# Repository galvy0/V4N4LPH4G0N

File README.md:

# V4N4LPH4G0N

Alpha stagger version of the V4N4G0N.  

Heavily referenced V4N4G0RTH0N: https://github.com/jpuerto96/V4N4G0RTH0N

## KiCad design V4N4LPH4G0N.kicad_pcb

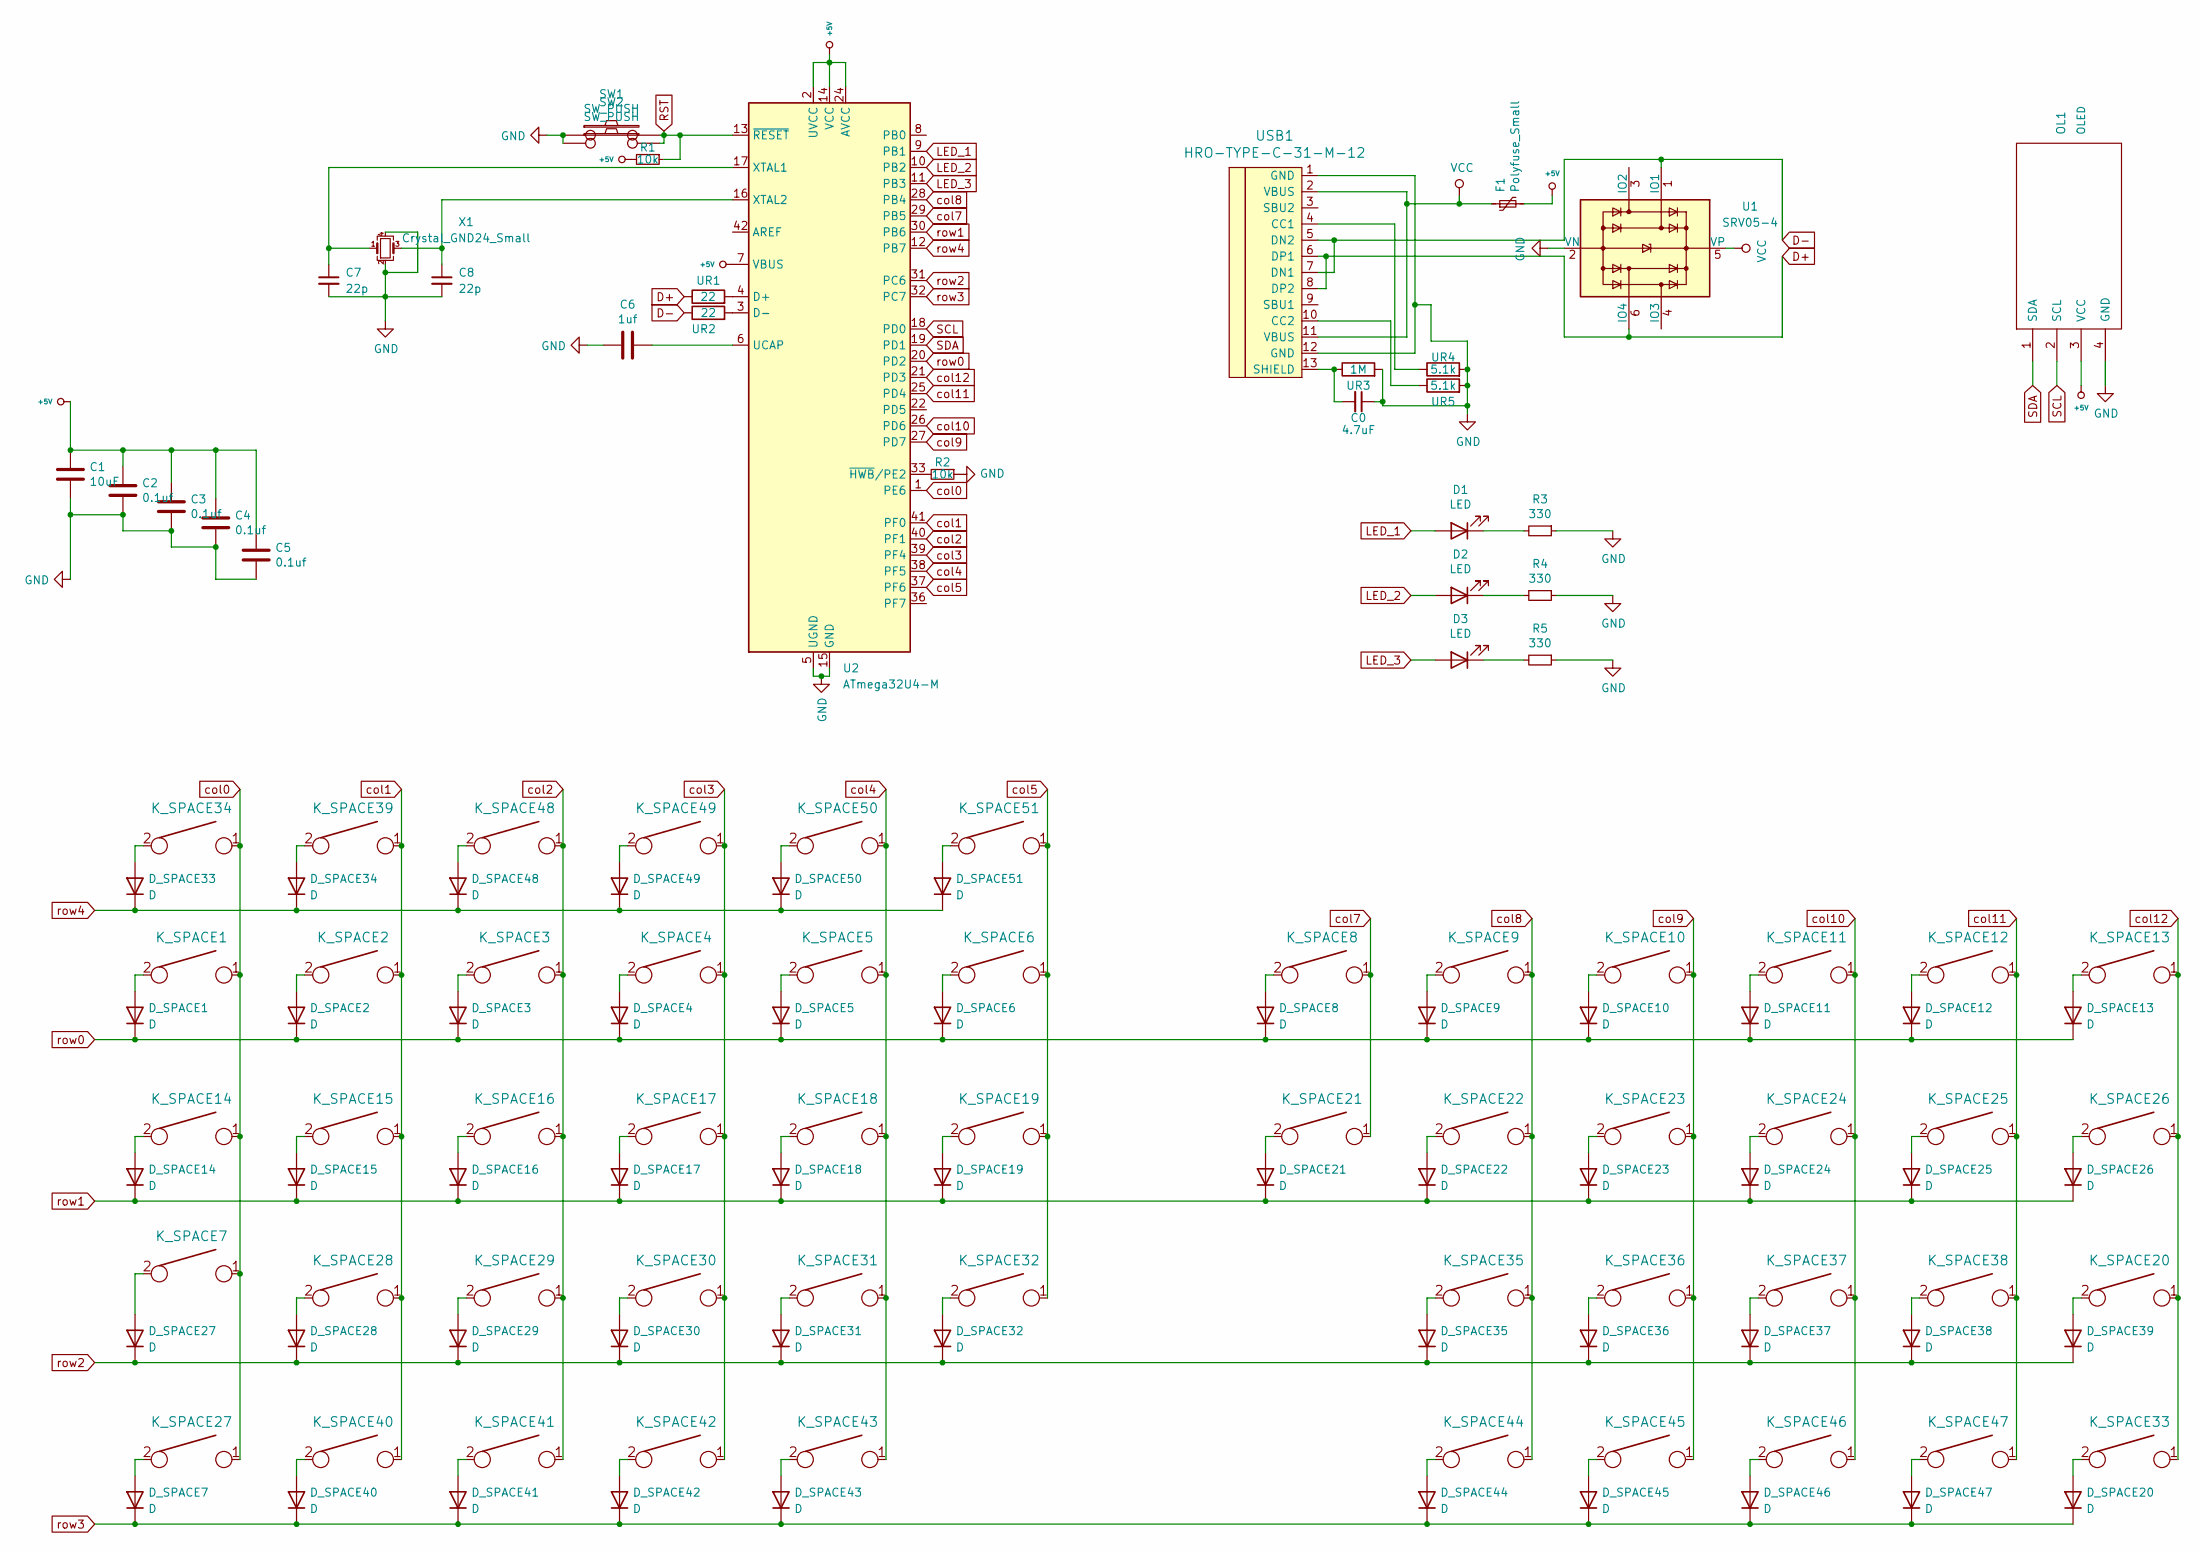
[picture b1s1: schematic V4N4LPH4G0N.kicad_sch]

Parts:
C0: 4.7uF; C_0805_2012Metric_Pad1.18x1.45mm_HandSolder
C1: 10uF; C_0805_2012Metric_Pad1.18x1.45mm_HandSolder
C2, C3, C4, C5: 0.1uf; C_0805_2012Metric_Pad1.18x1.45mm_HandSolder
C6: 1uf; C_0805_2012Metric_Pad1.18x1.45mm_HandSolder
C7, C8: 22p; C_0805_2012Metric_Pad1.18x1.45mm_HandSolder
D1, D2, D3: LED; LED_D3.0mm
D_SPACE1, D_SPACE2, D_SPACE3, D_SPACE4, D_SPACE5, D_SPACE6, D_SPACE7, D_SPACE8, D_SPACE9, D_SPACE10, D_SPACE11, D_SPACE12, D_SPACE13, D_SPACE14, D_SPACE15, D_SPACE16, D_SPACE17, D_SPACE18, D_SPACE19, D_SPACE20, D_SPACE21, D_SPACE22, D_SPACE23, D_SPACE24, D_SPACE25, D_SPACE26, D_SPACE27, D_SPACE28, D_SPACE29, D_SPACE30, D_SPACE31, D_SPACE32, D_SPACE33, D_SPACE34, D_SPACE35, D_SPACE36, D_SPACE37, D_SPACE38, D_SPACE39, D_SPACE40, D_SPACE41, D_SPACE42, D_SPACE43, D_SPACE44, D_SPACE45, D_SPACE46, D_SPACE47, D_SPACE48, D_SPACE49, D_SPACE50, D_SPACE51: D; D_SOD-123
F1: Polyfuse_Small; Fuse_1206_3216Metric_Pad1.42x1.75mm_HandSolder
K_SPACE1, K_SPACE2, K_SPACE3, K_SPACE4, K_SPACE5, K_SPACE6, K_SPACE8, K_SPACE9, K_SPACE10, K_SPACE11, K_SPACE12, K_SPACE13, K_SPACE14, K_SPACE15, K_SPACE16, K_SPACE17, K_SPACE18, K_SPACE19, K_SPACE21, K_SPACE22, K_SPACE23, K_SPACE24, K_SPACE25, K_SPACE26, K_SPACE28, K_SPACE29, K_SPACE30, K_SPACE31, K_SPACE34, K_SPACE35, K_SPACE36, K_SPACE37, K_SPACE38, K_SPACE39, K_SPACE42, K_SPACE45, K_SPACE48, K_SPACE49, K_SPACE50, K_SPACE51: KEYSW; MXOnly-1U-NoLED
K_SPACE7, K_SPACE20, K_SPACE43: KEYSW; MXOnly-1.5U-NoLED
K_SPACE27, K_SPACE33, K_SPACE40, K_SPACE41, K_SPACE46, K_SPACE47: KEYSW; MXOnly-1.25U-NoLED
K_SPACE32, K_SPACE44: KEYSW; MXOnly-1.75U-NoLED
OL1: OLED; OLED_v2
R1, R2: 10k; R_0805_2012Metric_Pad1.20x1.40mm_HandSolder
R3, R4, R5: 330; R_0805_2012Metric
SW1, SW2: SW_PUSH; SW_SPST_SKQG_WithoutStem
U1: SRV05-4; SOT-23-6_Handsoldering
U2: ATmega32U4-M; QFN-44-1EP_7x7mm_P0.5mm_EP5.2x5.2mm_ThermalVias
UR1, UR2: 22; R_0805_2012Metric_Pad1.20x1.40mm_HandSolder
UR3: 1M; R_0805_2012Metric_Pad1.20x1.40mm_HandSolder
UR4, UR5: 5.1k; R_0805_2012Metric_Pad1.20x1.40mm_HandSolder
USB1: HRO-TYPE-C-31-M-12; HRO-TYPE-C-31-M-12-HandSoldering
X1: Crystal_GND24_Small; Crystal_SMD_3225-4Pin_3.2x2.5mm_HandSoldering

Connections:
+5V: C1.1, C2.1, C3.1, C4.1, C5.1, F1.2, OL1.3 (VCC), R1.2, U2.2 (UVCC), U2.7 (VBUS), U2.14 (VCC), U2.24 (AVCC), U2.34 (VCC), U2.44 (AVCC)
D+: U1.6 (IO4), UR2.1, USB1.6 (DP1), USB1.8 (DP2)
D-: U1.1 (IO1), UR1.1, USB1.5 (DN2), USB1.7 (DN1)
GND: C0.1, C1.2, C2.2, C3.2, C4.2, C5.2, C6.2, C7.2, C8.2, OL1.4 (GND), R2.1, R3.1, R4.1, R5.1, SW1.1, SW2.1, U1.2 (VN), U2.5 (UGND), U2.15 (GND), U2.23 (GND), U2.35 (GND), U2.43 (GND), U2.45 (GND), UR3.2, UR4.2, UR5.2, USB1.1 (GND), USB1.12 (GND), X1.2, X1.4
LED_1: D1.2 (A), U2.9 (PB1)
LED_2: D2.2 (A), U2.10 (PB2)
LED_3: D3.2 (A), U2.11 (PB3)
unnamed: C0.2, UR3.1, USB1.13 (SHIELD)
unnamed: C6.1, U2.6 (UCAP)
unnamed: C7.1, U2.17 (XTAL1), X1.1
unnamed: C8.1, U2.16 (XTAL2), X1.3
unnamed: D1.1 (K), R3.2
unnamed: D2.1 (K), R4.2
unnamed: D3.1 (K), R5.2
unnamed: D_SPACE1.2 (A), K_SPACE1.2
unnamed: D_SPACE2.2 (A), K_SPACE2.2
unnamed: D_SPACE3.2 (A), K_SPACE3.2
unnamed: D_SPACE4.2 (A), K_SPACE4.2
unnamed: D_SPACE5.2 (A), K_SPACE5.2
unnamed: D_SPACE6.2 (A), K_SPACE6.2
unnamed: D_SPACE7.2 (A), K_SPACE27.2
unnamed: D_SPACE8.2 (A), K_SPACE8.2
unnamed: D_SPACE9.2 (A), K_SPACE9.2
unnamed: D_SPACE10.2 (A), K_SPACE10.2
unnamed: D_SPACE11.2 (A), K_SPACE11.2
unnamed: D_SPACE12.2 (A), K_SPACE12.2
unnamed: D_SPACE13.2 (A), K_SPACE13.2
unnamed: D_SPACE14.2 (A), K_SPACE14.2
unnamed: D_SPACE15.2 (A), K_SPACE15.2
unnamed: D_SPACE16.2 (A), K_SPACE16.2
unnamed: D_SPACE17.2 (A), K_SPACE17.2
unnamed: D_SPACE18.2 (A), K_SPACE18.2
unnamed: D_SPACE19.2 (A), K_SPACE19.2
unnamed: D_SPACE20.2 (A), K_SPACE33.2
unnamed: D_SPACE21.2 (A), K_SPACE21.2
unnamed: D_SPACE22.2 (A), K_SPACE22.2
unnamed: D_SPACE23.2 (A), K_SPACE23.2
unnamed: D_SPACE24.2 (A), K_SPACE24.2
unnamed: D_SPACE25.2 (A), K_SPACE25.2
unnamed: D_SPACE26.2 (A), K_SPACE26.2
unnamed: D_SPACE27.2 (A), K_SPACE7.2
unnamed: D_SPACE28.2 (A), K_SPACE28.2
unnamed: D_SPACE29.2 (A), K_SPACE29.2
unnamed: D_SPACE30.2 (A), K_SPACE30.2
unnamed: D_SPACE31.2 (A), K_SPACE31.2
unnamed: D_SPACE32.2 (A), K_SPACE32.2
unnamed: D_SPACE33.2 (A), K_SPACE34.2
unnamed: D_SPACE34.2 (A), K_SPACE39.2
unnamed: D_SPACE35.2 (A), K_SPACE35.2
unnamed: D_SPACE36.2 (A), K_SPACE36.2
unnamed: D_SPACE37.2 (A), K_SPACE37.2
unnamed: D_SPACE38.2 (A), K_SPACE38.2
unnamed: D_SPACE39.2 (A), K_SPACE20.2
unnamed: D_SPACE40.2 (A), K_SPACE40.2
unnamed: D_SPACE41.2 (A), K_SPACE41.2
unnamed: D_SPACE42.2 (A), K_SPACE42.2
unnamed: D_SPACE43.2 (A), K_SPACE43.2
unnamed: D_SPACE44.2 (A), K_SPACE44.2
unnamed: D_SPACE45.2 (A), K_SPACE45.2
unnamed: D_SPACE46.2 (A), K_SPACE46.2
unnamed: D_SPACE47.2 (A), K_SPACE47.2
unnamed: D_SPACE48.2 (A), K_SPACE48.2
unnamed: D_SPACE49.2 (A), K_SPACE49.2
unnamed: D_SPACE50.2 (A), K_SPACE50.2
unnamed: D_SPACE51.2 (A), K_SPACE51.2
unnamed: R2.2, U2.33 (~HWB/PE2)
unnamed: U2.3 (D-), UR1.2
unnamed: U2.4 (D+), UR2.2
unnamed: UR4.1, USB1.4 (CC1)
unnamed: UR5.1, USB1.10 (CC2)
RST: R1.1, SW1.2, SW2.2, U2.13 (~RESET)
SCL: OL1.2 (SCL), U2.18 (PD0)
SDA: OL1.1 (SDA), U2.19 (PD1)
VCC: F1.1, U1.5 (VP), USB1.2 (VBUS), USB1.11 (VBUS)
col0: K_SPACE1.1, K_SPACE7.1, K_SPACE14.1, K_SPACE27.1, K_SPACE34.1, U2.1 (PE6)
col1: K_SPACE2.1, K_SPACE15.1, K_SPACE28.1, K_SPACE39.1, K_SPACE40.1, U2.41 (PF0)
col2: K_SPACE3.1, K_SPACE16.1, K_SPACE29.1, K_SPACE41.1, K_SPACE48.1, U2.40 (PF1)
col3: K_SPACE4.1, K_SPACE17.1, K_SPACE30.1, K_SPACE42.1, K_SPACE49.1, U2.39 (PF4)
col4: K_SPACE5.1, K_SPACE18.1, K_SPACE31.1, K_SPACE43.1, K_SPACE50.1, U2.38 (PF5)
col5: K_SPACE6.1, K_SPACE19.1, K_SPACE32.1, K_SPACE51.1, U2.37 (PF6)
col7: K_SPACE8.1, K_SPACE21.1, U2.29 (PB5)
col8: K_SPACE9.1, K_SPACE22.1, K_SPACE35.1, K_SPACE44.1, U2.28 (PB4)
col9: K_SPACE10.1, K_SPACE23.1, K_SPACE36.1, K_SPACE45.1, U2.27 (PD7)
col10: K_SPACE11.1, K_SPACE24.1, K_SPACE37.1, K_SPACE46.1, U2.26 (PD6)
col11: K_SPACE12.1, K_SPACE25.1, K_SPACE38.1, K_SPACE47.1, U2.25 (PD4)
col12: K_SPACE13.1, K_SPACE20.1, K_SPACE26.1, K_SPACE33.1, U2.21 (PD3)
row0: D_SPACE1.1 (K), D_SPACE2.1 (K), D_SPACE3.1 (K), D_SPACE4.1 (K), D_SPACE5.1 (K), D_SPACE6.1 (K), D_SPACE8.1 (K), D_SPACE9.1 (K), D_SPACE10.1 (K), D_SPACE11.1 (K), D_SPACE12.1 (K), D_SPACE13.1 (K), U2.20 (PD2)
row1: D_SPACE14.1 (K), D_SPACE15.1 (K), D_SPACE16.1 (K), D_SPACE17.1 (K), D_SPACE18.1 (K), D_SPACE19.1 (K), D_SPACE21.1 (K), D_SPACE22.1 (K), D_SPACE23.1 (K), D_SPACE24.1 (K), D_SPACE25.1 (K), D_SPACE26.1 (K), U2.30 (PB6)
row2: D_SPACE27.1 (K), D_SPACE28.1 (K), D_SPACE29.1 (K), D_SPACE30.1 (K), D_SPACE31.1 (K), D_SPACE32.1 (K), D_SPACE35.1 (K), D_SPACE36.1 (K), D_SPACE37.1 (K), D_SPACE38.1 (K), D_SPACE39.1 (K), U2.31 (PC6)
row3: D_SPACE7.1 (K), D_SPACE20.1 (K), D_SPACE40.1 (K), D_SPACE41.1 (K), D_SPACE42.1 (K), D_SPACE43.1 (K), D_SPACE44.1 (K), D_SPACE45.1 (K), D_SPACE46.1 (K), D_SPACE47.1 (K), U2.32 (PC7)
row4: D_SPACE33.1 (K), D_SPACE34.1 (K), D_SPACE48.1 (K), D_SPACE49.1 (K), D_SPACE50.1 (K), D_SPACE51.1 (K), U2.12 (PB7)

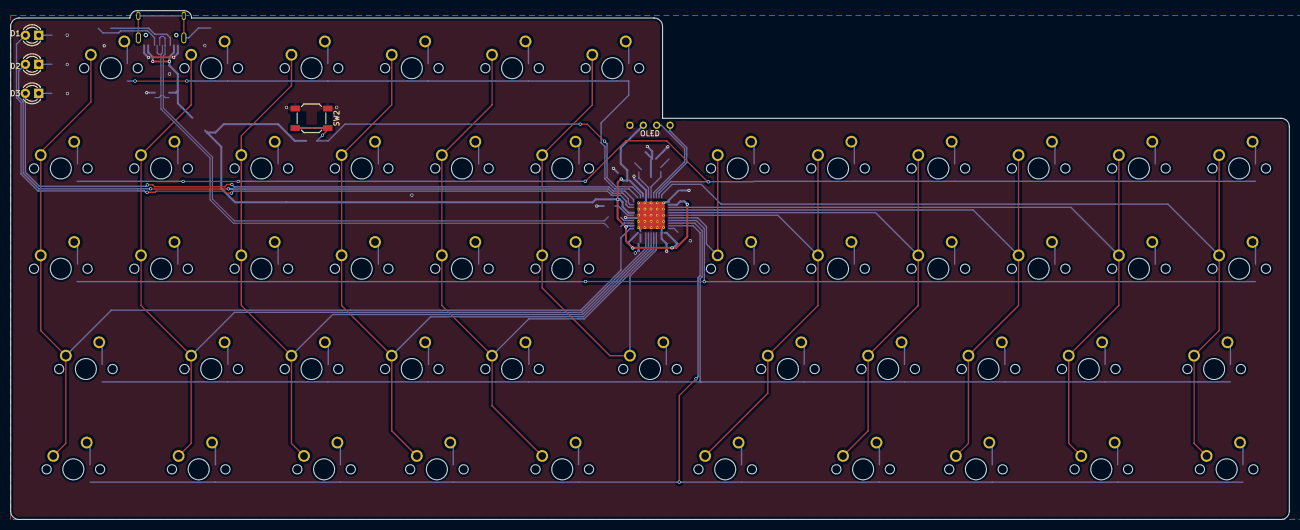
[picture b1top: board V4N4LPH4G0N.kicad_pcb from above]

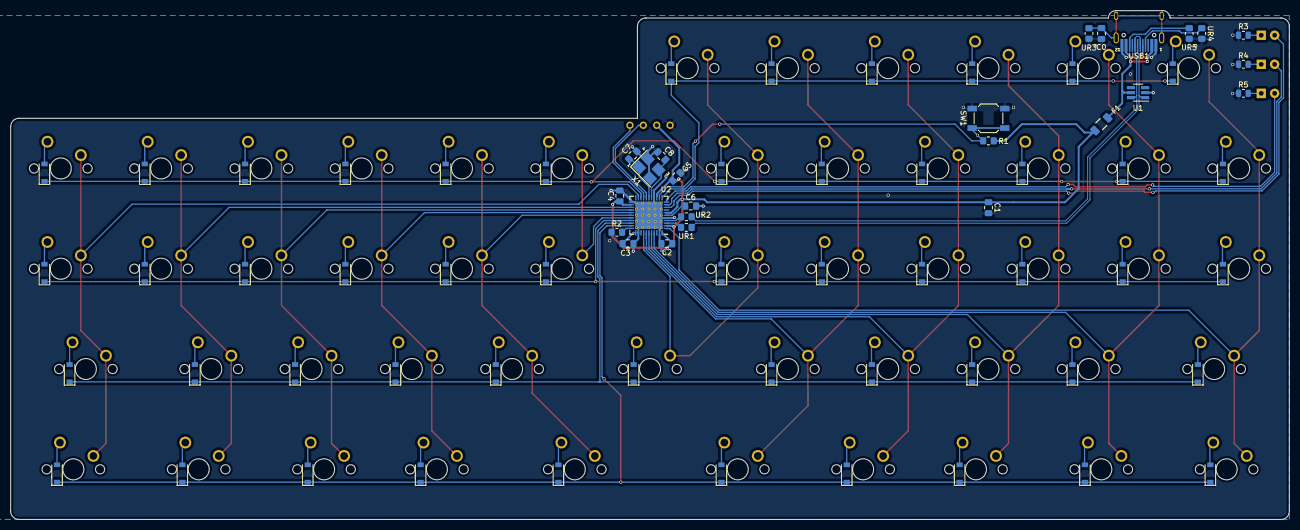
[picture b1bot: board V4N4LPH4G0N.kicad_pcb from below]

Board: 2 copper layers, 242.9 x 96.6 mm, 132 parts (76 on the bottom side), 91 nets.

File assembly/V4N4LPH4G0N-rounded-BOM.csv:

sep=;
"Id";"Designator";"Package";"Quantity";"Designation";"Supplier and ref";
1;"K_SPACE30,K_SPACE31,K_SPACE38,K_SPACE22,K_SPACE11,K_SPACE42,K_SPACE1,K_SPACE51,K_SPACE12,K_SPACE2,K_SPACE50,K_SPACE10,K_SPACE37,K_SPACE34,K_SPACE24,K_SPACE9,K_SPACE15,K_SPACE48,K_SPACE17,K_SPACE16,K_SPACE25,K_SPACE21,K_SPACE28,K_SPACE35,K_SPACE6,K_SPACE14,K_SPACE49,K_SPACE3,K_SPACE19,K_SPACE13,K_SPACE5,K_SPACE26,K_SPACE39,K_SPACE36,K_SPACE18,K_SPACE45,K_SPACE8,K_SPACE29,K_SPACE23,K_SPACE4";"MXOnly-1U-NoLED";40;"KEYSW";;;
2;"K_SPACE40,K_SPACE46,K_SPACE33,K_SPACE41,K_SPACE27,K_SPACE47";"MXOnly-1.25U-NoLED";6;"KEYSW";;;
3;"SW2,SW1";"SW_SPST_SKQG_WithoutStem";2;"SW_PUSH";;;
4;"D3,D2,D1";"LED_D3.0mm";3;"LED";;;
5;"K_SPACE43,K_SPACE7,K_SPACE20";"MXOnly-1.5U-NoLED";3;"KEYSW";;;
6;"K_SPACE44,K_SPACE32";"MXOnly-1.75U-NoLED";2;"KEYSW";;;
7;"OL1";"OLED_v2";1;"OLED";;;
8;"D_SPACE29,D_SPACE50,D_SPACE30,D_SPACE44,D_SPACE26,D_SPACE22,D_SPACE16,D_SPACE13,D_SPACE43,D_SPACE45,D_SPACE33,D_SPACE20,D_SPACE34,D_SPACE7,D_SPACE25,D_SPACE28,D_SPACE39,D_SPACE2,D_SPACE14,D_SPACE46,D_SPACE11,D_SPACE4,D_SPACE8,D_SPACE19,D_SPACE42,D_SPACE12,D_SPACE23,D_SPACE36,D_SPACE32,D_SPACE3,D_SPACE24,D_SPACE31,D_SPACE37,D_SPACE38,D_SPACE10,D_SPACE6,D_SPACE5,D_SPACE27,D_SPACE41,D_SPACE35,D_SPACE21,D_SPACE49,D_SPACE18,D_SPACE9,D_SPACE17,D_SPACE15,D_SPACE51,D_SPACE48,D_SPACE1,D_SPACE40,D_SPACE47";"D_SOD-123";51;"D";;;
9;"R4,R5,R3";"R_0805_2012Metric";3;"330";;;
10;"UR2,UR1";"R_0805_2012Metric_Pad1.20x1.40mm_HandSolder";2;"22";;;
11;"X1";"Crystal_SMD_3225-4Pin_3.2x2.5mm_HandSoldering";1;"Crystal_GND24_Small";;;
12;"C0";"C_0805_2012Metric_Pad1.18x1.45mm_HandSolder";1;"4.7uF";;;
13;"C2,C4,C5,C3";"C_0805_2012Metric_Pad1.18x1.45mm_HandSolder";4;"0.1uf";;;
14;"R2,R1";"R_0805_2012Metric_Pad1.20x1.40mm_HandSolder";2;"10k";;;
15;"U2";"QFN-44-1EP_7x7mm_P0.5mm_EP5.2x5.2mm_ThermalVias";1;"ATmega32U4-M";;;
16;"C8,C7";"C_0805_2012Metric_Pad1.18x1.45mm_HandSolder";2;"22p";;;
17;"C6";"C_0805_2012Metric_Pad1.18x1.45mm_HandSolder";1;"1uf";;;
18;"UR3";"R_0805_2012Metric_Pad1.20x1.40mm_HandSolder";1;"1M";;;
19;"C1";"C_0805_2012Metric_Pad1.18x1.45mm_HandSolder";1;"10uF";;;
20;"UR4,UR5";"R_0805_2012Metric_Pad1.20x1.40mm_HandSolder";2;"5.1k";;;
21;"USB1";"HRO-TYPE-C-31-M-12-HandSoldering";1;"HRO-TYPE-C-31-M-12";;;
22;"U1";"SOT-23-6_Handsoldering";1;"SRV05-4";;;
23;"F1";"Fuse_1206_3216Metric_Pad1.42x1.75mm_HandSolder";1;"Polyfuse_Small";;;

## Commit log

2022-12-31 init
2023-01-04 rename;plate
2023-01-05 route
2023-01-06 rename; finish design
2023-01-07 fixed solder mask missing
